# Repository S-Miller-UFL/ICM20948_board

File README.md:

This is a breakout board for the STM32F072.

It contains a 9-axis ICM-20948 IMU chip, and a AT25SF081 SPI serial flash chip for storing data from the IMU.

All you need to do is to place it directly on top of the master STM32 board, and its ready to go.

The design was made in KICAD. Its traced, routed, and ready for manufacturing.

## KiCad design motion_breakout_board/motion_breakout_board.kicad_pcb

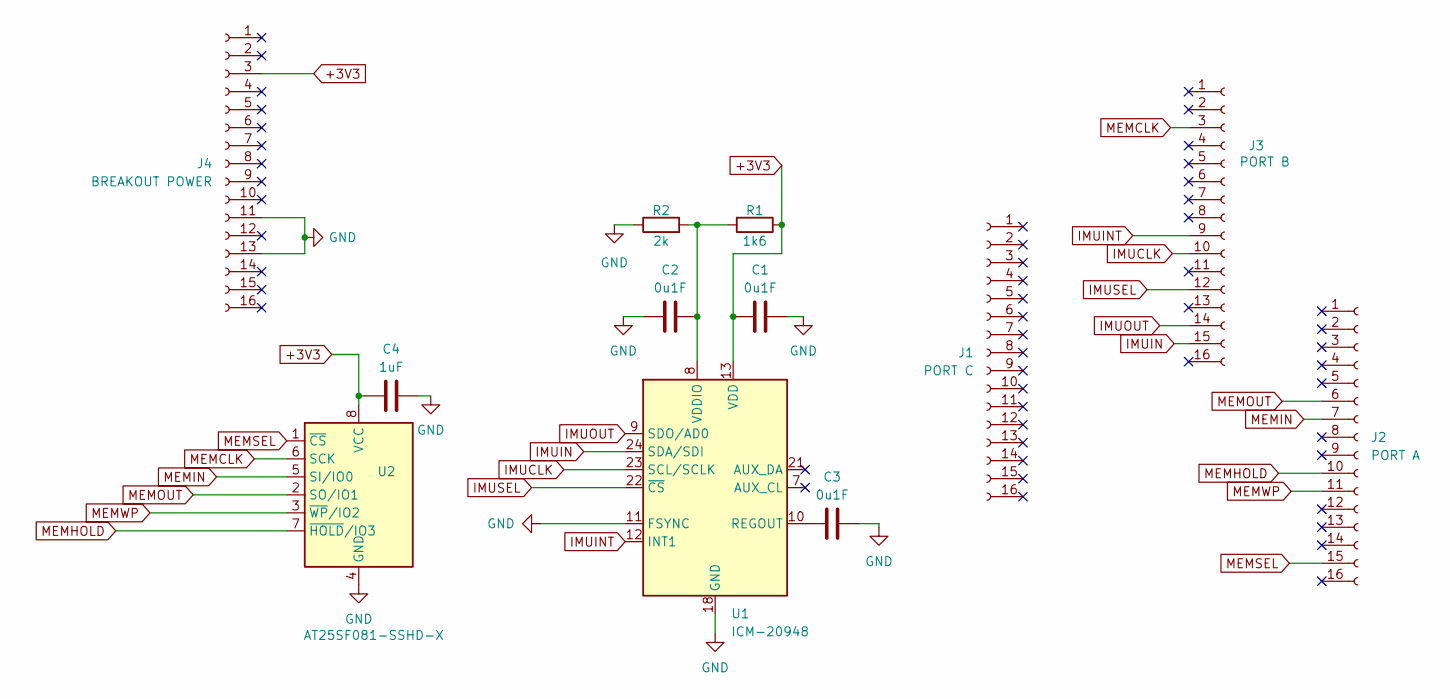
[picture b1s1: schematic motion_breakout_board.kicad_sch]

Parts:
C1, C2, C3: 0u1F; C_0603_1608Metric
C4: 1uF; C_0603_1608Metric
J1: PORT C; PinSocket_1x16_P2.00mm_Vertical
J2: PORT A; PinSocket_1x16_P2.00mm_Vertical
J3: PORT B; PinSocket_1x16_P2.00mm_Vertical
J4: BREAKOUT POWER; PinSocket_1x16_P2.00mm_Vertical
R1: 1k6; C_0603_1608Metric
R2: 2k; C_0603_1608Metric
U1: ICM-20948; InvenSense_QFN-24_3x3mm_P0.4mm
U2: AT25SF081-SSHD-X; SOIC-8_3.9x4.9mm_P1.27mm

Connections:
+3V3: C1.1, C4.1, J4.3, R1.1, U1.13 (VDD), U2.8 (VCC)
GND: C1.2, C2.1, C3.2, C4.2, J4.11, J4.13, R2.1, U1.11 (FSYNC), U1.18 (GND), U1.20 (GND), U2.4 (GND)
IMUCLK: J3.10, U1.23 (SCL/SCLK)
IMUIN: J3.15, U1.24 (SDA/SDI)
IMUINT: J3.9, U1.12 (INT1)
IMUOUT: J3.14, U1.9 (SDO/AD0)
IMUSEL: J3.12, U1.22 (~CS)
MEMCLK: J3.3, U2.6 (SCK)
MEMHOLD: J2.10, U2.7 (~HOLD/IO3)
MEMIN: J2.7, U2.5 (SI/IO0)
MEMOUT: J2.6, U2.2 (SO/IO1)
MEMSEL: J2.15, U2.1 (~CS)
MEMWP: J2.11, U2.3 (~WP/IO2)
unnamed: C3.1, U1.10 (REGOUT)
unnamed: C2.2, R1.2, R2.2, U1.8 (VDDIO)

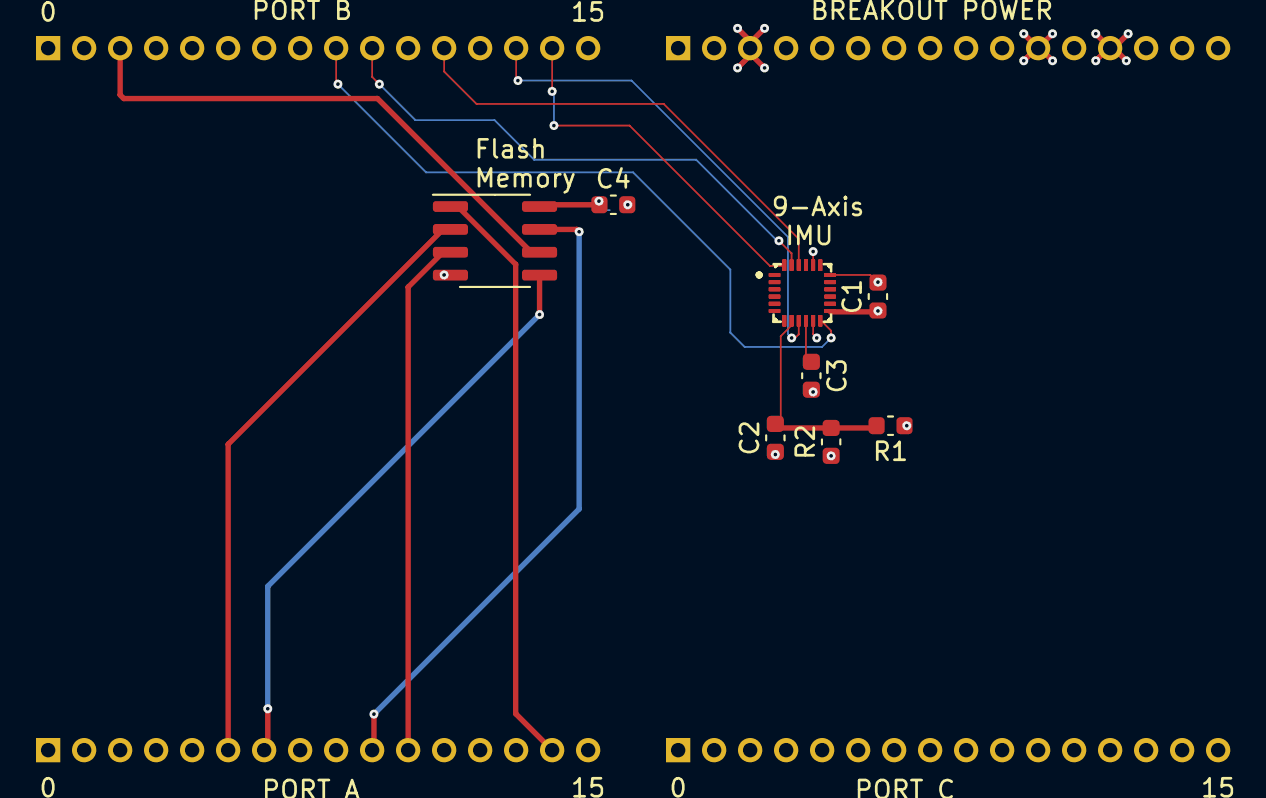
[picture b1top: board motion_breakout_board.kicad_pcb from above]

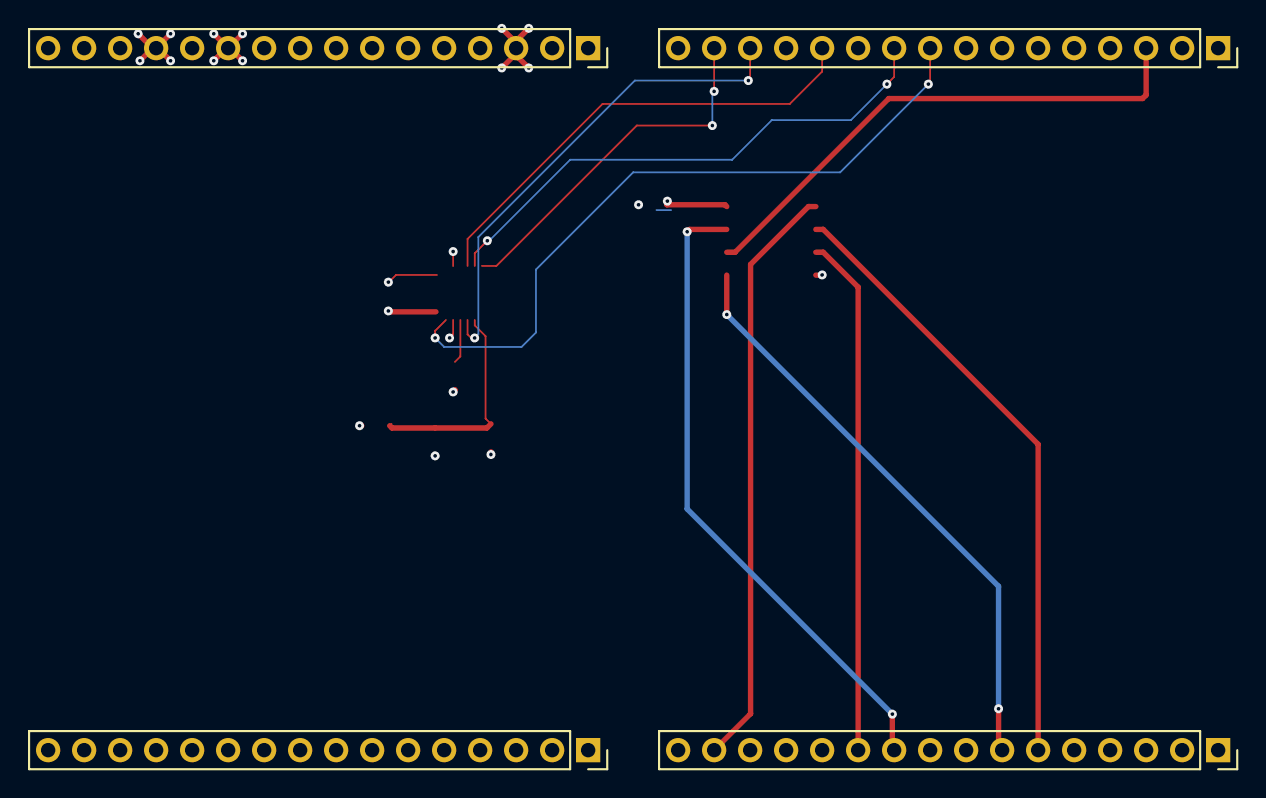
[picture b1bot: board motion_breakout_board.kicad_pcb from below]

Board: 4 copper layers, 12 parts (4 on the bottom side), 15 nets.

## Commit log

2024-12-27 Created README.md
